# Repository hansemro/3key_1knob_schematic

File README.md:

3 Key + 1 Knob Minipad Schematic
================================

This repo contains an approximate KiCAD schematic and PCB layout for a 3 Key + 1 Knob minipad with
a CH552 USB MCU. Keys are each lit with an addressable NeoPixel (or similar) RGB LED.

## License

This work is licensed under a
[Creative Commons Attribution 4.0 International License][cc-by].

[![CC BY 4.0][cc-by-image]][cc-by]

[cc-by]: http://creativecommons.org/licenses/by/4.0/
[cc-by-image]: https://i.creativecommons.org/l/by/4.0/88x31.png

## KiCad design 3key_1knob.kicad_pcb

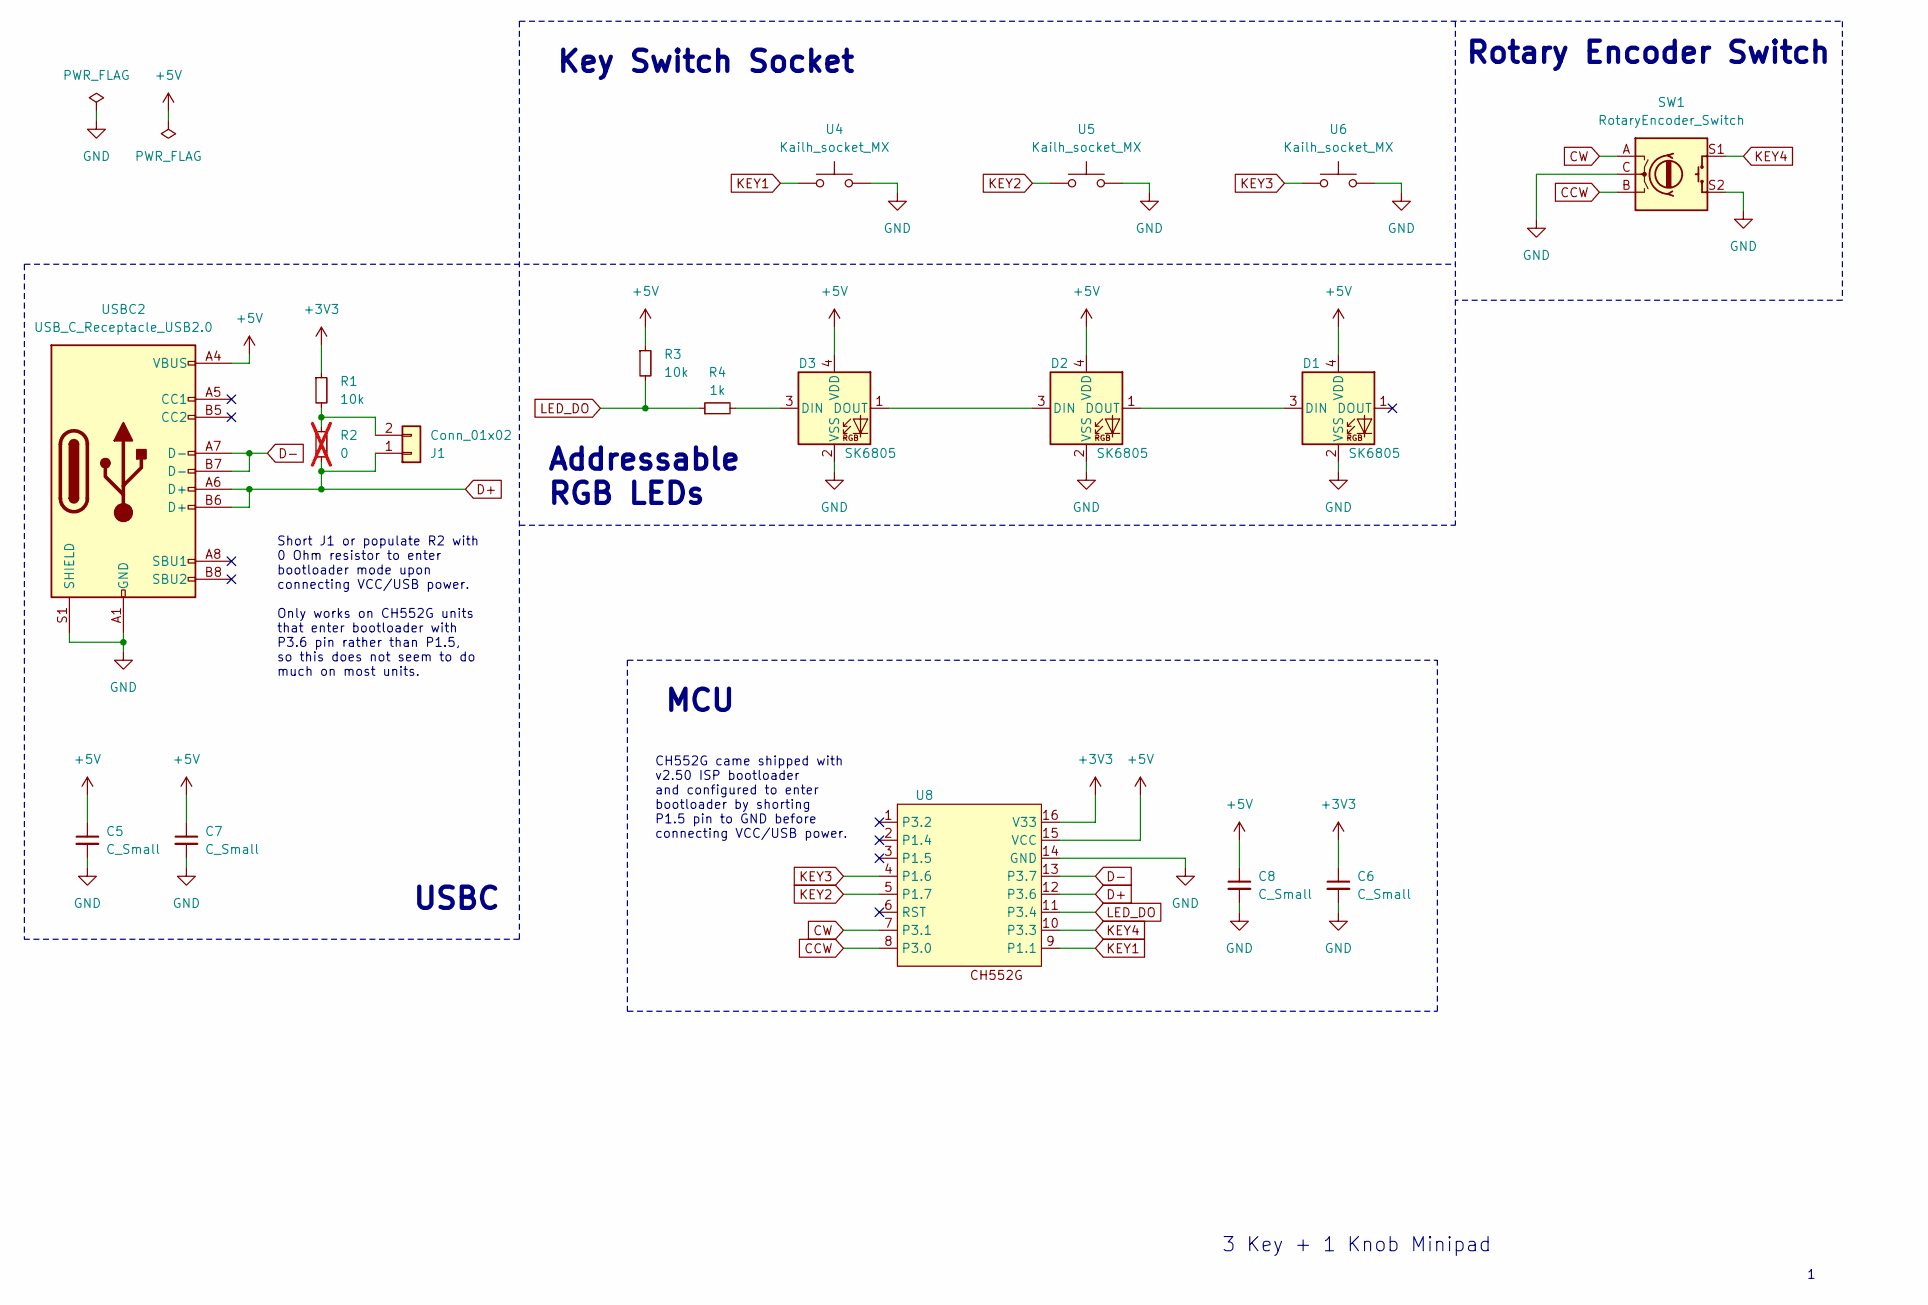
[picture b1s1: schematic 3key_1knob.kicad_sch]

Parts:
C5, C6, C7, C8: C_Small; C_0603_1608Metric
D1, D2, D3: SK6805; LED_SK6805_PLCC4_2.4x2.7mm_P1.3mm
J1: Conn_01x02; PinHeader_1x02_P1.27mm_Vertical
R1, R3: 10k; R_0603_1608Metric
R2: 0; R_0603_1608Metric; not fitted
R4: 1k; R_0603_1608Metric
SW1: RotaryEncoder_Switch; RotaryEncoder_Alps_EC12E-Switch_Vertical_H20mm
U4, U5, U6: Kailh_socket_MX
U8: SOP-16_3.9x9.9mm_P1.27mm
USBC2: USB_C_Receptacle_USB2.0; USB_C_Receptacle_GCT_USB4105-xx-A_16P_TopMnt_Horizontal

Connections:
+3V3: C6.1, R1.1, U8.16 (V33)
+5V: C5.1, C7.1, C8.1, D1.4 (VDD), D2.4 (VDD), D3.4 (VDD), R3.1, U8.15 (VCC), USBC2.A4 (VBUS), USBC2.A9 (VBUS), USBC2.B4 (VBUS), USBC2.B9 (VBUS)
CCW: SW1.B, U8.8 (P3.0)
CW: SW1.A, U8.7 (P3.1)
D+: J1.1, R2.2, U8.12 (P3.6), USBC2.A6 (D+), USBC2.B6 (D+)
D-: U8.13 (P3.7), USBC2.A7 (D-), USBC2.B7 (D-)
GND: C5.2, C6.2, C7.2, C8.2, D1.2 (VSS), D2.2 (VSS), D3.2 (VSS), SW1.C, SW1.S2, U4.2, U5.2, U6.2, U8.14 (GND), USBC2.A1 (GND), USBC2.A12 (GND), USBC2.B1 (GND), USBC2.B12 (GND), USBC2.S1 (SHIELD)
KEY1: U4.1, U8.9 (P1.1)
KEY2: U5.1, U8.5 (P1.7)
KEY3: U6.1, U8.4 (P1.6)
KEY4: SW1.S1, U8.10 (P3.3)
LED_DO: R3.2, R4.1, U8.11 (P3.4)
unnamed: D1.3 (DIN), D2.1 (DOUT)
unnamed: D2.3 (DIN), D3.1 (DOUT)
unnamed: D3.3 (DIN), R4.2
unnamed: J1.2, R1.2, R2.1

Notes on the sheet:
3 Key + 1 Knob Minipad
Short J1 or populate R2 with 0 Ohm resistor to enter bootloader mode upon connecting VCC/USB power. Only works on CH552G units that enter bootloader with P3.6 pin rather than P1.5, so this does not seem to do much on most units.
USBC
Key Switch Socket
MCU
Rotary Encoder Switch
CH552G came shipped with v2.50 ISP bootloader and configured to enter bootloader by shorting P1.5 pin to GND before connecting VCC/USB power.
Addressable RGB LEDs

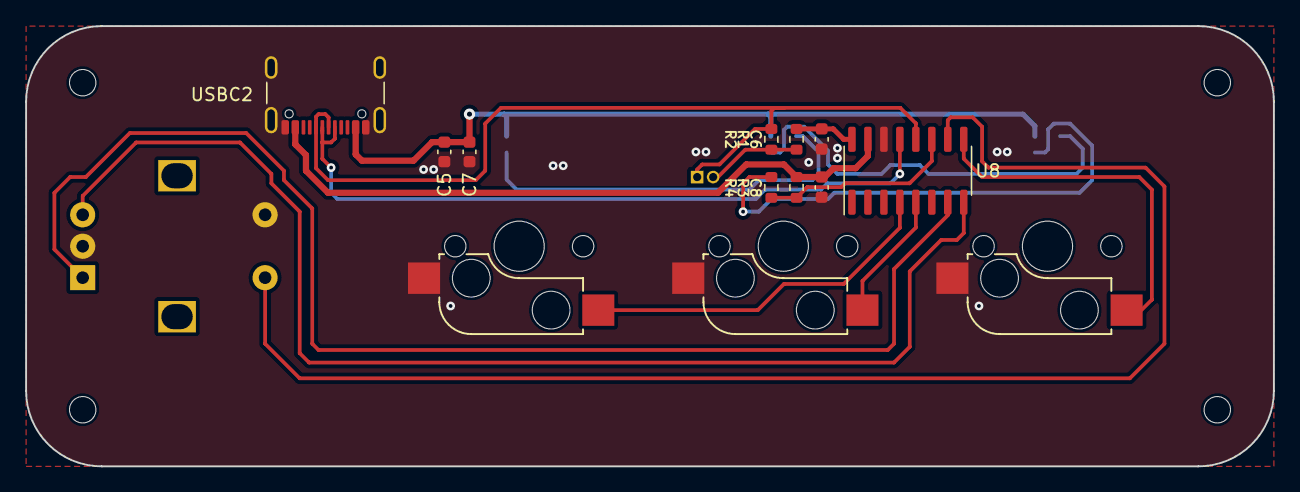
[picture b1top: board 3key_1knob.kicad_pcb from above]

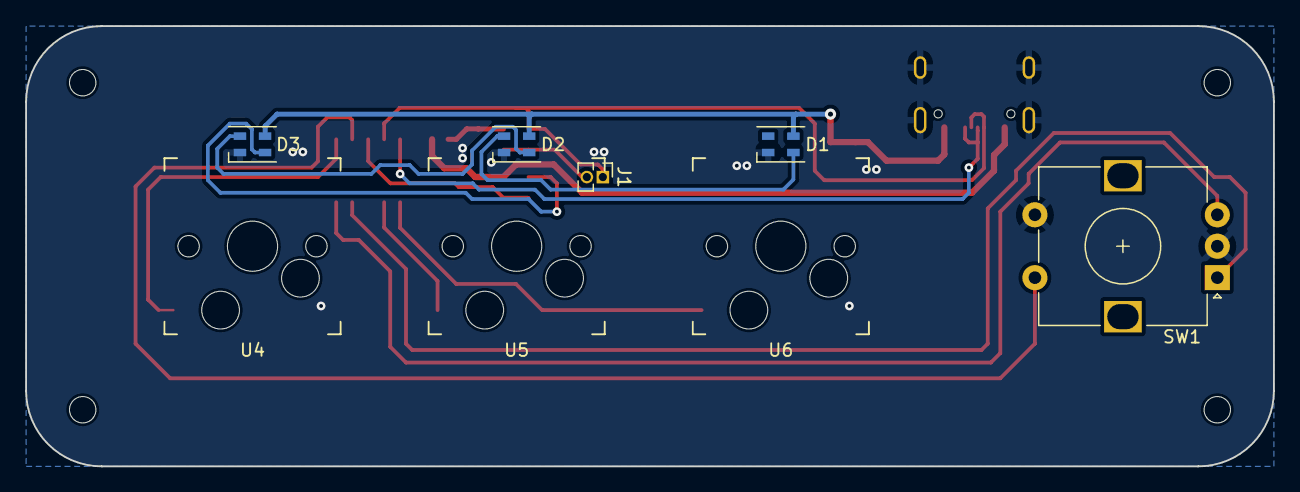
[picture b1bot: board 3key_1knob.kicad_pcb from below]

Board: 2 copper layers, 99.2 x 35.0 mm, 18 parts (8 on the bottom side), 16 nets.

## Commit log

2023-11-10 Initial README.md
2023-11-10 [WIP] Initial schematic and PCB drawings
2023-11-11 Update PCB
2023-11-11 Unrouted PCB
2023-11-11 Remove drawings
2023-11-11 Use JLCPCB rules for 1-2 Layer PCB
2023-11-12 Route signals and power
2023-11-12 Finish ground fills; Add 2 pin header; Update 3D models
    This completes the PCB drawing based off the (questionable) original
    design. Due to odd signal routing, there are several ground fill islands
    that had to be addressed by placing microvias.
    Note that with JLCPCB DRC constraints, there will be some spacing
    violations due to the USBC footprint used. The USBC footprint has 2
    mounting holes which are too close to power pads.
2023-11-12 Route LED_DO signal to MCU; Adjust trace thickness and ground fills
    This routes LED_DO which was previously unconnected to MCU, as well as
    increase trace thickness and use thermal relief pad connections on
    bottom ground fills.
    Thickness of power traces decreased to 0.5.
    Thickness of signal traces increased to 0.3.
2023-11-13 Minor PCB update
2023-11-20 Adjust LED positions and traces for better accuracy
2023-11-20 Connect USBC receptacle and Rotary Encoder shield to ground; Adjust traces
2023-11-20 Update PCB measurement drawings
2023-11-20 Use solid ground fill for front layer (again)
    This reverts change that made front ground fill use thermal reliefs for
    pads due to introducing DRC violations around certain ground pads.
    Fixes: 05fae067c ("Connect USBC receptacle and Rotary Encoder shield to
    ground")
2023-11-20 Add mounting holes around corners
2023-11-20 Convert signal nets to global nets; Update sch description; Minor PCB trace update
2023-11-20 License work under CC-BY-4.0
2023-11-22 README.md: remove license shield
